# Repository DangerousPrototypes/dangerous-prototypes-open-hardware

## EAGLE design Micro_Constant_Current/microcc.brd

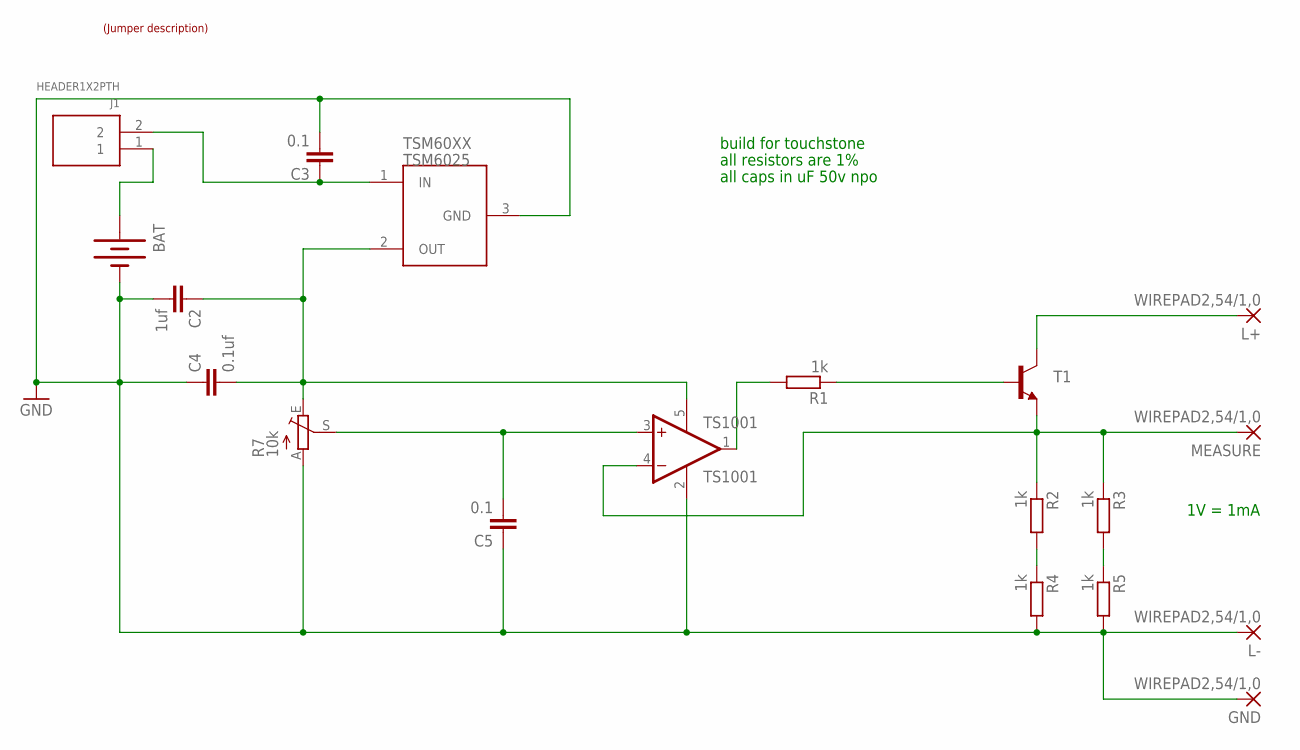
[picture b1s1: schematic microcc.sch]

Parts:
BAT: BATTERY20SMD; BATTCON_20MM
C2: 1uf; C603
C3, C5: 0.1; C603
C4: 0.1uf; C603
GND: WIREPAD2,54/1,0; 2,54/1,0
J1: HEADER1X2PTH; M1X2
L+: WIREPAD2,54/1,0; 2,54/1,0
L-: WIREPAD2,54/1,0; 2,54/1,0
MEASURE: WIREPAD2,54/1,0; 2,54/1,0
R1, R2, R3, R4, R5: 1k; R603
R7: 10k; PT-SPIN
T1: TRANSISTOR_NPNSOT23; SOT23
TS1001: TS1001; SC70-5L
TSM6025: TSM60XX; SOT23
U$1: JUMP2_DESC

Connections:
GND: BAT.2 (-), C2.2, C3.2, C4.1, C5.1, GND.1, L-.1, R4.2, R5.2, R7.A, TS1001.2 (V-), TSM6025.3 (GND)
unnamed: R1.1, T1.1 (B)
unnamed: R2.2, R4.1
unnamed: R1.2, TS1001.1 (OUT)
unnamed: C2.1, C4.2, R7.E, TS1001.5 (V+), TSM6025.2 (OUT)
unnamed: C3.1, J1.2, TSM6025.1 (IN)
unnamed: R3.2, R5.1
unnamed: BAT.1 (+), J1.1
unnamed: C5.2, R7.S, TS1001.3 (+IN)
unnamed: L+.1, T1.3 (C)
unnamed: MEASURE.1, R2.1, R3.1, T1.2 (E), TS1001.4 (-IN)

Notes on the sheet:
1V = 1mA
all resistors are 1%
all caps in uF 50v npo
build for touchstone

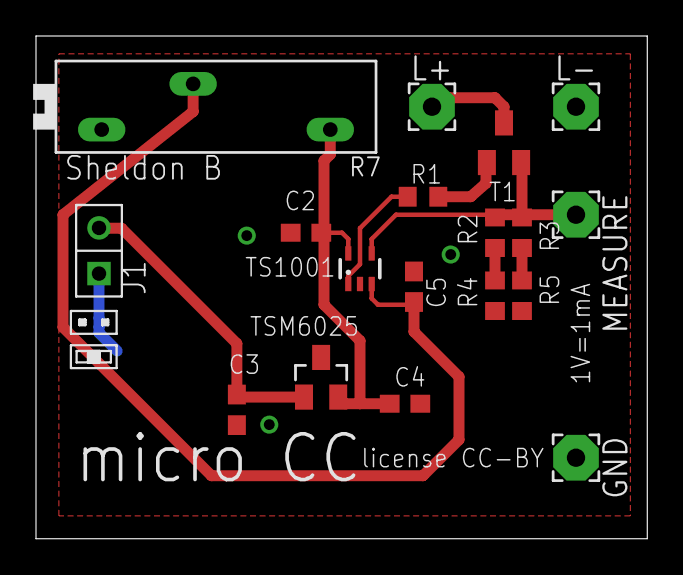
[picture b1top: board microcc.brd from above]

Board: 2 copper layers, 34.0 x 27.9 mm, 20 parts (1 on the bottom side), 11 nets.

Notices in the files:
Micro_Constant_Current/microcc.brd:
license CC-BY
parts and their libraries:
SparkFun: Licensing: CC v3.0 Share-Alike You are welcome to use this library for commercial purposes.
